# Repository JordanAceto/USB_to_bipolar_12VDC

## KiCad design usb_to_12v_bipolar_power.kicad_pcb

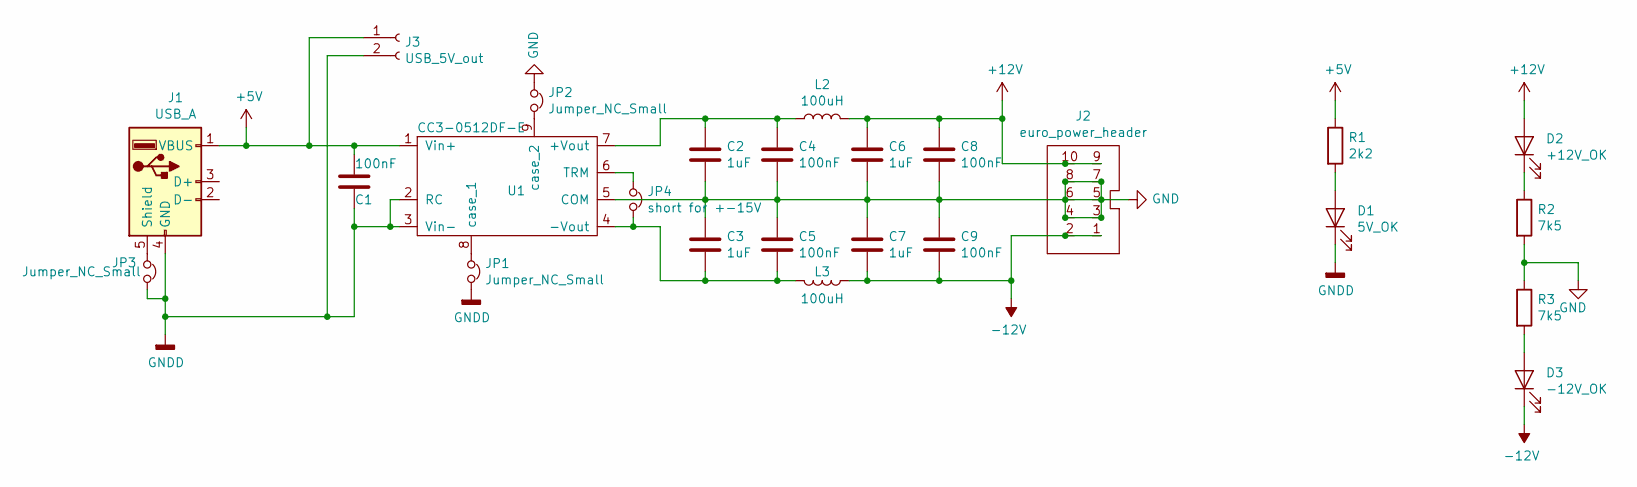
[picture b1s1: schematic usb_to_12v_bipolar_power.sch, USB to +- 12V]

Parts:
C1, C4, C5, C8, C9: 100nF; C_0805_2012Metric_Pad1.15x1.40mm_HandSolder
C2, C3, C6, C7: 1uF; C_0805_2012Metric_Pad1.15x1.40mm_HandSolder
D1: 5V_OK; LED_0805_2012Metric_Pad1.15x1.40mm_HandSolder
D2: +12V_OK; LED_0805_2012Metric_Pad1.15x1.40mm_HandSolder
D3: -12V_OK; LED_0805_2012Metric_Pad1.15x1.40mm_HandSolder
J1: USB_A; MUSBR-A111-X-X
J2: euro_power_header; eurorack_power_header
J3: USB_5V_out; PinSocket_1x02_P2.54mm_Vertical
JP1, JP2, JP3: Jumper_NC_Small; C_0805_2012Metric_Pad1.15x1.40mm_HandSolder
JP4: short for +-15V; C_0805_2012Metric_Pad1.15x1.40mm_HandSolder
L2, L3: 100uH; L_0805_2012Metric_Pad1.15x1.40mm_HandSolder
R1: 2k2; R_0805_2012Metric_Pad1.15x1.40mm_HandSolder
R2, R3: 7k5; R_0805_2012Metric_Pad1.15x1.40mm_HandSolder
U1: CC3-0512DF-E

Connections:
+5V: C1.1, J1.1 (VBUS), J3.1, R1.1, U1.1 (Vin+)
+12V: C6.1, C8.1, D2.2 (A), J2.9, J2.10, L2.2
-12V: C7.2, C9.2, D3.1 (K), J2.1, J2.2, L3.1
GND: C2.2, C3.1, C4.2, C5.1, C6.2, C7.1, C8.2, C9.1, J2.3, J2.4, J2.5, J2.6, J2.7, J2.8, JP2.1, R2.2, R3.1, U1.5 (COM)
GNDD: C1.2, D1.1 (K), J1.4 (GND), J3.2, JP1.2, JP3.2, U1.2 (RC), U1.3 (Vin-)
unnamed: C2.1, C4.1, L2.1, U1.7 (+Vout)
unnamed: C3.2, C5.2, JP4.2, L3.2, U1.4 (-Vout)
unnamed: D1.2 (A), R1.2
unnamed: D2.1 (K), R2.1
unnamed: D3.2 (A), R3.2
unnamed: J1.5 (Shield), JP3.1
unnamed: JP1.1, U1.8 (case_1)
unnamed: JP2.2, U1.9 (case_2)
unnamed: JP4.1, U1.6 (TRM)

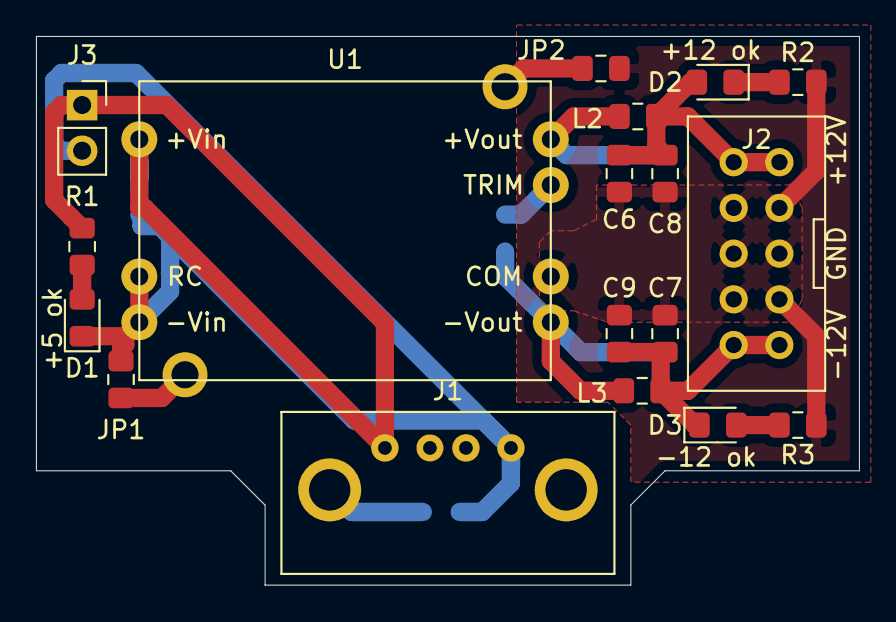
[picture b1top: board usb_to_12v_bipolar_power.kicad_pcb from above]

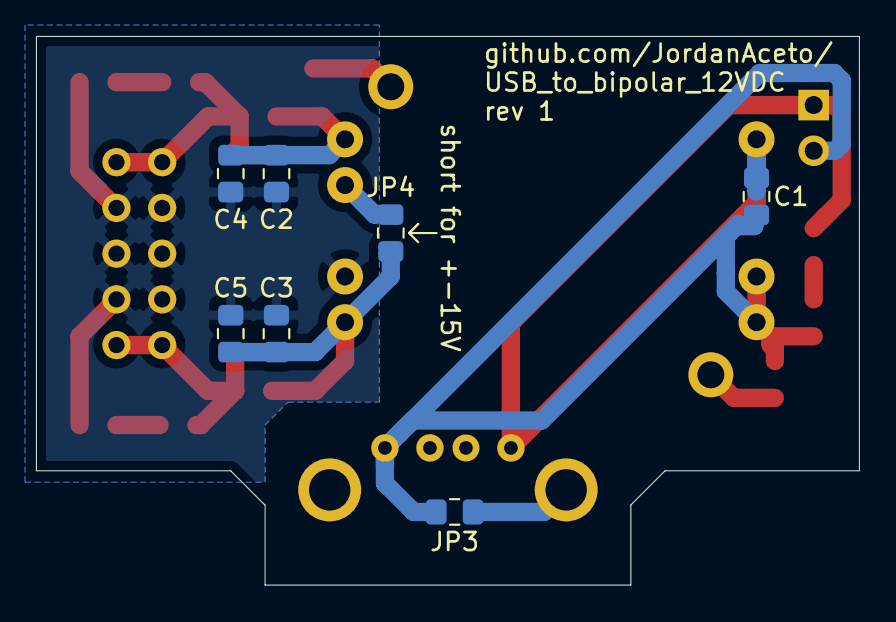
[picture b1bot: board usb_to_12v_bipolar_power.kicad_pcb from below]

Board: 2 copper layers, 45.7 x 30.5 mm, 25 parts (7 on the bottom side), 14 nets.

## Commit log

2019-05-24 add BOM
2019-05-24 remove old redundant BOM
2019-05-24 add link to mouser project to BOM
2019-05-24 add pdf of schematic
2019-05-24 add jpegs of board front and back
2019-05-24 add github link to pcb silkscreen
2020-03-16 change usb type, big pcb changes
2020-03-16 update pcb images and schematic

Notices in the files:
usb_to_12v_bipolar_power.kicad_pcb:
License: CC by 4.0
usb_to_12v_bipolar_power.sch:
creativecommons.org/licenses/by/4.0
